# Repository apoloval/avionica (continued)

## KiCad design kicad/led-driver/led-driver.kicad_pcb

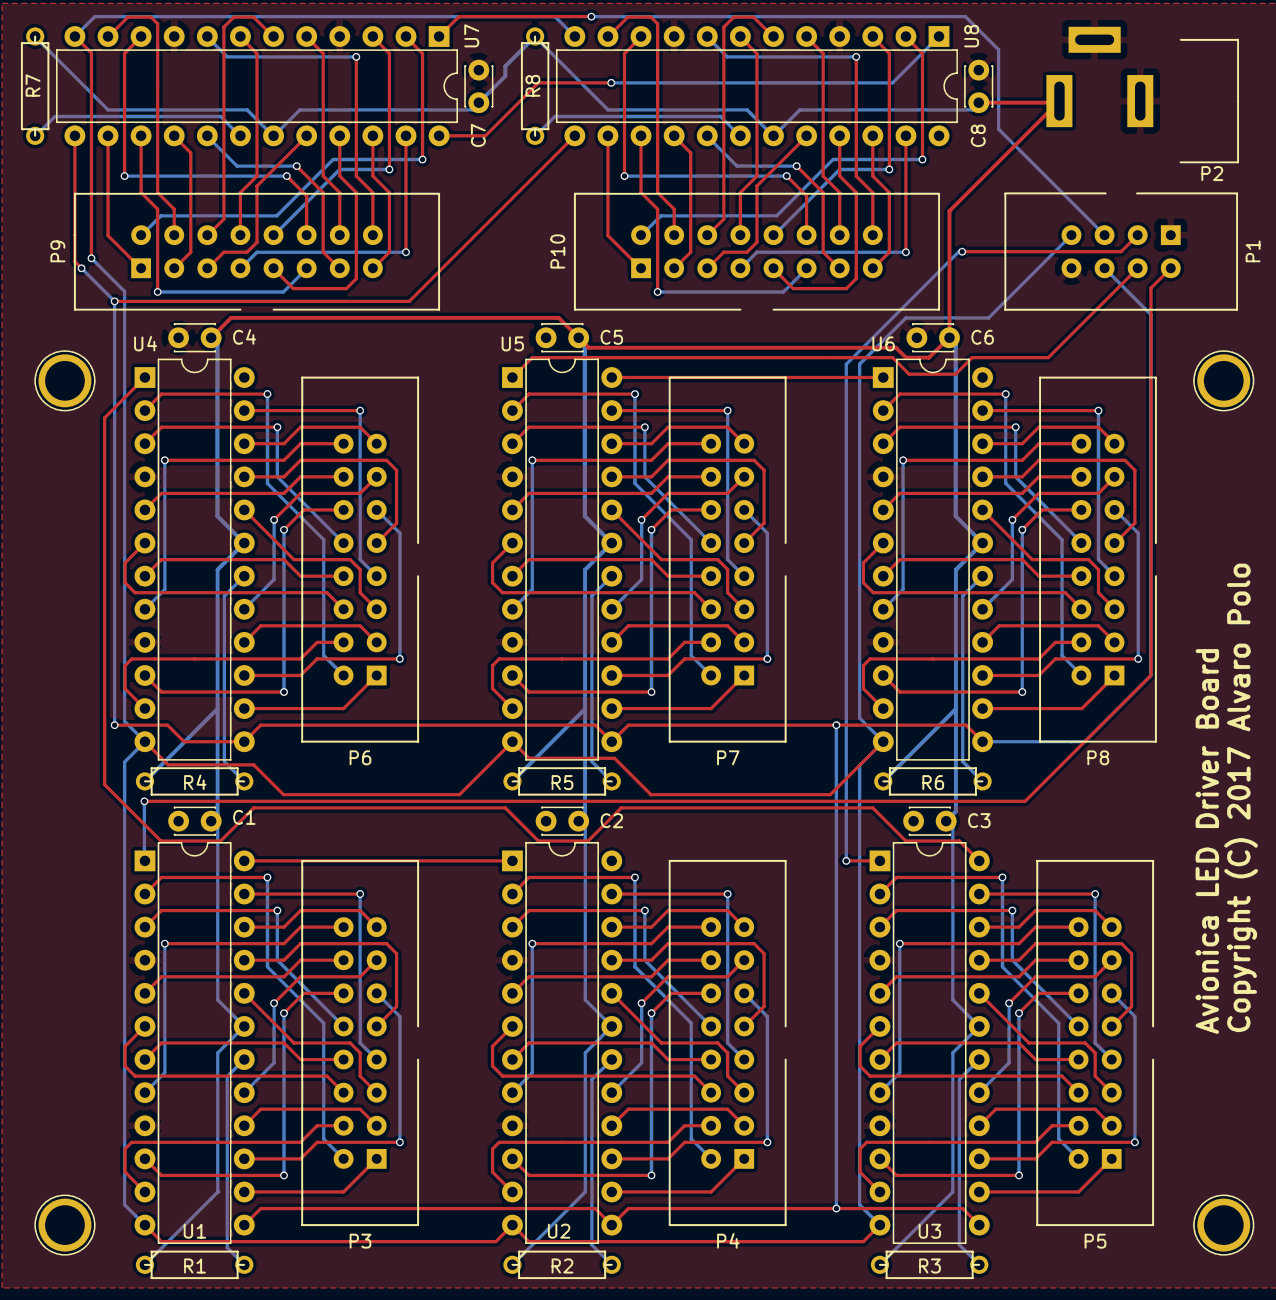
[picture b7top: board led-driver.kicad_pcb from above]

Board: 2 copper layers, 34 parts (0 on the bottom side), 148 nets.

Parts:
C1, C2, C3, C4, C5, C6, C7, C8: C_Small; C_Disc_D3.0mm_W2.0mm_P2.50mm
P1: CONN_02X04; idc-8p
P2: CONN_01X03; Jack_55_21
P3, P4, P5, P6, P7, P8, P9, P10: CONN_02X08; idc-16p
R1, R2, R3, R4, R5, R6, R7, R8: R; R3
U1, U2, U3, U4, U5, U6, U7, U8: MAX7219; DIP-24_W7.62mm

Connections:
/CLOCK: P1.6, U1.13, U2.13, U3.13, U4.13, U5.13, U6.13, U7.13, U8.13
/LATCH: P1.7, U1.12, U2.12, U3.12, U4.12, U5.12, U6.12, U7.12, U8.12
/LINE-A/DIG.1.0: P3.2, U1.2
/LINE-A/DIG.1.1: P3.4, U1.11
/LINE-A/DIG.1.2: P3.6, U1.6
/LINE-A/DIG.1.3: P3.8, U1.7
/LINE-A/DIG.1.4: P3.10, U1.3
/LINE-A/DIG.1.5: P3.12, U1.10
/LINE-A/DIG.1.6: P3.14, U1.5
/LINE-A/DIG.1.7: P3.16, U1.8
/LINE-A/DIG.2.0: P4.2, U2.2
/LINE-A/DIG.2.1: P4.4, U2.11
/LINE-A/DIG.2.2: P4.6, U2.6
/LINE-A/DIG.2.3: P4.8, U2.7
/LINE-A/DIG.2.4: P4.10, U2.3
/LINE-A/DIG.2.5: P4.12, U2.10
/LINE-A/DIG.2.6: P4.14, U2.5
/LINE-A/DIG.2.7: P4.16, U2.8
/LINE-A/SEG1.A: P3.1, U1.14
/LINE-A/SEG1.B: P3.3, U1.16
/LINE-A/SEG1.C: P3.5, U1.20
/LINE-A/SEG1.D: P3.7, U1.23
/LINE-A/SEG1.DP: P3.15, U1.22
/LINE-A/SEG1.E: P3.9, U1.21
/LINE-A/SEG1.F: P3.11, U1.15
/LINE-A/SEG1.G: P3.13, U1.17
/LINE-A/SEG2.A: P4.1, U2.14
/LINE-A/SEG2.B: P4.3, U2.16
/LINE-A/SEG2.C: P4.5, U2.20
/LINE-A/SEG2.D: P4.7, U2.23
/LINE-A/SEG2.DP: P4.15, U2.22
/LINE-A/SEG2.E: P4.9, U2.21
/LINE-A/SEG2.F: P4.11, U2.15
/LINE-A/SEG2.G: P4.13, U2.17
/LINE-B/DIG.1.0: P5.2, U3.2
/LINE-B/DIG.1.1: P5.4, U3.11
/LINE-B/DIG.1.2: P5.6, U3.6
/LINE-B/DIG.1.3: P5.8, U3.7
/LINE-B/DIG.1.4: P5.10, U3.3
/LINE-B/DIG.1.5: P5.12, U3.10
/LINE-B/DIG.1.6: P5.14, U3.5
/LINE-B/DIG.1.7: P5.16, U3.8
/LINE-B/DIG.2.0: P6.2, U4.2
/LINE-B/DIG.2.1: P6.4, U4.11
/LINE-B/DIG.2.2: P6.6, U4.6
/LINE-B/DIG.2.3: P6.8, U4.7
/LINE-B/DIG.2.4: P6.10, U4.3
/LINE-B/DIG.2.5: P6.12, U4.10
/LINE-B/DIG.2.6: P6.14, U4.5
/LINE-B/DIG.2.7: P6.16, U4.8
/LINE-B/SEG1.A: P5.1, U3.14
/LINE-B/SEG1.B: P5.3, U3.16
/LINE-B/SEG1.C: P5.5, U3.20
/LINE-B/SEG1.D: P5.7, U3.23
/LINE-B/SEG1.DP: P5.15, U3.22
/LINE-B/SEG1.E: P5.9, U3.21
/LINE-B/SEG1.F: P5.11, U3.15
/LINE-B/SEG1.G: P5.13, U3.17
/LINE-B/SEG2.A: P6.1, U4.14
/LINE-B/SEG2.B: P6.3, U4.16
/LINE-B/SEG2.C: P6.5, U4.20
/LINE-B/SEG2.D: P6.7, U4.23
/LINE-B/SEG2.DP: P6.15, U4.22
/LINE-B/SEG2.E: P6.9, U4.21
/LINE-B/SEG2.F: P6.11, U4.15
/LINE-B/SEG2.G: P6.13, U4.17
/LINE-C/DIG.1.0: P7.2, U5.2
/LINE-C/DIG.1.1: P7.4, U5.11
/LINE-C/DIG.1.2: P7.6, U5.6
/LINE-C/DIG.1.3: P7.8, U5.7
/LINE-C/DIG.1.4: P7.10, U5.3
/LINE-C/DIG.1.5: P7.12, U5.10
/LINE-C/DIG.1.6: P7.14, U5.5
/LINE-C/DIG.1.7: P7.16, U5.8
/LINE-C/DIG.2.0: P8.2, U6.2
/LINE-C/DIG.2.1: P8.4, U6.11
/LINE-C/DIG.2.2: P8.6, U6.6
/LINE-C/DIG.2.3: P8.8, U6.7
/LINE-C/DIG.2.4: P8.10, U6.3
/LINE-C/DIG.2.5: P8.12, U6.10
/LINE-C/DIG.2.6: P8.14, U6.5
/LINE-C/DIG.2.7: P8.16, U6.8
/LINE-C/SEG1.A: P7.1, U5.14
/LINE-C/SEG1.B: P7.3, U5.16
/LINE-C/SEG1.C: P7.5, U5.20
/LINE-C/SEG1.D: P7.7, U5.23
/LINE-C/SEG1.DP: P7.15, U5.22
/LINE-C/SEG1.E: P7.9, U5.21
/LINE-C/SEG1.F: P7.11, U5.15
/LINE-C/SEG1.G: P7.13, U5.17
/LINE-C/SEG2.A: P8.1, U6.14
/LINE-C/SEG2.B: P8.3, U6.16
/LINE-C/SEG2.C: P8.5, U6.20
/LINE-C/SEG2.D: P8.7, U6.23
/LINE-C/SEG2.DP: P8.15, U6.22
/LINE-C/SEG2.E: P8.9, U6.21
/LINE-C/SEG2.F: P8.11, U6.15
/LINE-C/SEG2.G: P8.13, U6.17
/LINE-D/DIG.1.0: P9.2, U7.2
/LINE-D/DIG.1.1: P9.4, U7.11
/LINE-D/DIG.1.2: P9.6, U7.6
/LINE-D/DIG.1.3: P9.8, U7.7
/LINE-D/DIG.1.4: P9.10, U7.3
/LINE-D/DIG.1.5: P9.12, U7.10
/LINE-D/DIG.1.6: P9.14, U7.5
/LINE-D/DIG.1.7: P9.16, U7.8
/LINE-D/DIG.2.0: P10.2, U8.2
/LINE-D/DIG.2.1: P10.4, U8.11
/LINE-D/DIG.2.2: P10.6, U8.6
/LINE-D/DIG.2.3: P10.8, U8.7
/LINE-D/DIG.2.4: P10.10, U8.3
/LINE-D/DIG.2.5: P10.12, U8.10
/LINE-D/DIG.2.6: P10.14, U8.5
/LINE-D/DIG.2.7: P10.16, U8.8
/LINE-D/SEG1.A: P9.1, U7.14
/LINE-D/SEG1.B: P9.3, U7.16
/LINE-D/SEG1.C: P9.5, U7.20
/LINE-D/SEG1.D: P9.7, U7.23
/LINE-D/SEG1.DP: P9.15, U7.22
/LINE-D/SEG1.E: P9.9, U7.21
/LINE-D/SEG1.F: P9.11, U7.15
/LINE-D/SEG1.G: P9.13, U7.17
/LINE-D/SEG2.A: P10.1, U8.14
/LINE-D/SEG2.B: P10.3, U8.16
/LINE-D/SEG2.C: P10.5, U8.20
/LINE-D/SEG2.D: P10.7, U8.23
/LINE-D/SEG2.DP: P10.15, U8.22
/LINE-D/SEG2.E: P10.9, U8.21
/LINE-D/SEG2.F: P10.11, U8.15
/LINE-D/SEG2.G: P10.13, U8.17
/LINE.A: P1.2, U1.1
/LINE.B: P1.3, U3.1
/LINE.C: P1.4, U5.1
/LINE.D: P1.5, U7.1
GND: C1.2, C2.2, C3.2, C4.2, C5.2, C6.2, C7.2, C8.2, P1.1, P1.8, P2.2, P2.3, U1.4, U1.9, U2.4, U2.9, U3.4, U3.9, U4.4, U4.9, U5.4, U5.9, U6.4, U6.9, U7.4, U7.9, U8.4, U8.9
unnamed: R1.2, U1.18
unnamed: R2.2, U2.18
unnamed: R3.2, U3.18
unnamed: R4.2, U4.18
unnamed: R5.2, U5.18
unnamed: R6.2, U6.18
unnamed: R7.2, U7.18
unnamed: R8.2, U8.18
unnamed: U1.24, U2.1
unnamed: U3.24, U4.1
unnamed: U5.24, U6.1
unnamed: U7.24, U8.1
VCC: C1.1, C2.1, C3.1, C4.1, C5.1, C6.1, C7.1, C8.1, P2.1, R1.1, R2.1, R3.1, R4.1, R5.1, R6.1, R7.1, R8.1, U1.19, U2.19, U3.19, U4.19, U5.19, U6.19, U7.19, U8.19

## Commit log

2016-02-10 Make it so
2016-02-10 Introduce Avionica library for Arduino
    With just minor functionality implemented.
2016-02-10 Improve `Avionica::Device` type in Arduino library
    The plan is to let the user to define different devices and declare
    the interactions of each device in a separate file.
2016-02-10 Reduce max number of devices for Arduino Uno
    To save RAM, limit them to 12. Actually the physical limit.
2016-02-11 Simplify private methods in Arduino library
2016-02-11 Introduce Avionica serial console in Arduino library
2016-02-11 Implement event interception in serial console mode for Arduino
2016-02-11 Rename console mode to debug mode in Arduino library
2016-02-14 New directory layout for Arduino libraries
    Putting all libraries in `arduino/libraries` will allocate space for
    more libraries.
2016-02-14 Fix typos in `BeforeInstall.txt`
2016-02-14 Move debug mode enabling to `begin()` function in Arduino library
2016-02-14 Integrate Avionica with Arduino OACSP library
2016-02-14 Add the ability to notify LVAR & FSUIPC events on devices
2016-02-15 Initialize OACSP from Avionica `begin()`
2016-02-15 Send reset command on device begin for Arduino library
2016-02-15 Update copyright notes in source files
2016-02-15 Introduce Avionica SPI for PIC microcontrollers
    A header file that can be included from XC8 projects to manage SPI.
2016-02-17 Add a README file for Arduino library
2016-02-18 Introduce basic structure of engine start panel device
2017-01-24 Make it so
    Import the existing files prior to have a Git repository.
2017-01-24 Add a mostly placeholder README file
2017-06-24 Add a gitignore file
2017-06-24 Adapt avionica ports to 6 pins
2017-06-24 Move Kicad files into its own subdir
2017-06-24 Add some VHDL files to simulate the modules
    By now, just an entity to simulate 74595 ICs. More coming in the future.
2017-06-24 VHDL: replace process by binding for 74595
2017-06-24 Make VHDL Makefile more robust
    Make it build when any dependency changes.
2017-06-24 VHDL: Add the serial out pin of 74595
2017-06-24 VHDL: clarify pin names in 74595
    Use the names from NXP datasheet and simplify the testbench.
2017-06-24 VHDL: add a new entity for 4021 parallel in serial out shift register
2017-06-26 Introduce scaffolding of a new PCB: A320 ECAM panel
2017-06-26 Initial schematic for A320 ECAM panel
2017-06-27 Adda RC circuit for CLR push buttons to debounce
2017-06-30 Use a polarized capacitor for CLR button of ECAM panel
2017-07-02 Use polarized cap for MM74C922's debounce in ECAM panel
2017-07-12 Fix Inverted columns and rows in 74C922 for ECAM panel
2017-07-12 Fix segment connections from MAX7219 in ECAM panel
2017-07-12 Add potentiometers to control ECAM display bright
    And also, reorganize the schematic to separate the different subsets of components.
2017-07-13 Add backlighting LEDs and power connectors to ECAM panel
2017-07-14 Fix wrong path to the Avionica module in A320 ECAM panel
2017-07-14 Add an axial resistor to the Avionica module
2017-07-14 Add a LED SMD 1210 to the Avionica module
2017-07-14 Add a disc capacitor to the Avionica module
2017-07-14 Add a radial capacitor to the Avionica module
2017-07-14 Add a Omron B3F push button to the Avionica module
2017-07-14 Add some pin headers to the Avionica module
2017-07-14 Add some associations to footprints in A320 ECAM panel
2017-07-14 Add some DIP housings to the Avionica module
2017-07-14 Replace power connectors by 3-line ones
    One for anode, two for cathode.
2017-07-14 Add the remaining footprint associations in A320 ECAM panel
2017-07-14 Add M3 mounting hole to the Avionica module
2017-07-28 Move potentiometer schematic to Avionica module
2017-07-28 Add a new Kicad project for a A320 engine start panel
2017-07-28 Add a rotary switch of 3 positions to the Avionica library
2017-07-28 Make the VCC pin non-visible in MAX7219
2017-07-28 Remove backup and cache files
2017-07-28 Prevent cached and backup files to be checkout
2017-07-28 Preliminary work on A320 ECAM panel PCB
2017-07-28 Adjust footprints layout in A320 ECAM panel
2017-07-28 Include some other backup files in the gitignore
2017-08-01 Make some final adjustments on footprints for A320 ECAM panel
2017-08-01 Complete the tracks of the PCB in A320 ECAM panel
2017-08-02 Include all necessary layers in plot selection for A320 ECAM panel
2017-09-30 Fix missing tracks in A320 ECAM panel
2017-09-30 Fix wrong width of Omron B3F pads
2017-09-30 Fix more missing pads in A320 ECAM panel
2017-09-30 Minor issues and label fixings in A320 ECAM panel
2017-10-08 Several changes in avionica library
    * Add 74125 part (3-state buffer)
    * Change the position of data pins in 74922
    * Set VCC pin as non-visible for MAX7219
2017-10-08 Add schematic for a IO Controller board
2017-10-08 Add a DIP-14 header for Avionica module
2017-10-08 Assign footprints for IO Controller board
2017-10-09 Ignore net files
2017-10-11 Simplify the IO Controller board schematics
2017-10-12 Fix several footprints to hide or remove undesired labels
2017-10-12 Several fixes in IO Controller board schematics
    * Remove extra unneeded decoupling capacitors.
    * Fix wrong orientation of dielectric capacitors
2017-10-12 First version of IO Controller panel PCB
2017-10-12 Add mounting holes to the IO Controller PCB
2017-10-12 Fix relative links to 3D models for several modules
2017-10-12 Add several layers in silkscreen for IO Controller board PCB
2017-10-12 Hide component label in IDC 10P footprint
2017-10-12 Use a single IDC10 connector for switches in IO Controller board
2017-10-12 Complete connections of IO Controller board PCB
2017-10-13 Add a new module for a IDC 6P angled
2017-10-13 Add OSHW logo to IO Controller board and fix some labels
2017-10-13 Use more appropriate models for capacitor footprints
2017-10-14 Fix non-DAVed key controllers problem in IO Controller board
2017-10-25 Add atmega328 microcontroller to the library
2017-10-25 Add a crystal component to Avionica library
2017-10-25 Fix wrong pin in atmega328
2017-10-25 Add a capacitor component to the Avionica library
2017-10-25 Add a connector of 6pins to Avionica library
2017-10-25 Add a connector of 3 pins to Avionica library
2017-10-25 A a crystal footprint for Avionica module
2017-10-25 Add a DIP-28 footprint for Avionica module
2017-10-25 Change the schematics of keypad controller to use an ATmega328
2017-10-25 Remove Avionica library DCM file
    It's only used for descriptions we don't really need.
2017-10-25 Add a resistor to the Avionica library
2017-10-25 Add a 8pin connector to the Avionica library
2017-10-25 Add 3D model for DIP-28 housing
2017-10-25 Add a MAX7219 to the keypad controller
2017-10-25 Prepare the layout of the Keypad Controller PCB
2017-11-01 Add the tracks to the Keypad Controller PCB
2017-11-01 Introduce a DAV signal in the Keypad Controller board
2017-11-01 Better alignment of oscillator capacitors in Keypad PCB
2017-11-01 Add a new component and module for a IDC 12P connector
2017-11-01 Replace 2x6p IDC connectors by a single 12p in Keypad Controller board
2017-11-01 Add a 12p connector to the Avionica library
2017-11-01 Replace 2x8p IDC connectors by a single 16p in Keypad Controller board
2017-11-01 Fix several issues in some footprints
2017-11-01 Add a LED component to the Avionica library
2017-11-01 Add a status LED to the Keypad Controller board
2017-11-01 Rename the files of Keypad Controller board
2017-11-23 Set some PCB printing settings for Keypad Controller board
2017-11-24 Introduce a Arduino sketch for the Avionica firmware
2017-12-29 Make Avionica firmware to send a connection header after setup
    It will be useful for the PC to wait for the board to be up and running and detect it is an actual Avionica board.
2017-12-29 Increase the drill size of IDC connectors
2017-12-29 Keypad controller Rev02: Update IDC connectors
2017-12-29 Use a directory layout to accomodate for new firmwares
    The main firmware we had corresponds to what we will call the Motherboard.
2017-12-29 Use explicit SPI settings in Motherboard firmware
    So we are sure about the modes we are using.
2017-12-29 Fix wrong read of input message in Motherboard firmware
2017-12-30 Fix wrong connection of ISET pin in Keypad Controller
2017-12-30 Add conn02 and conn04 to the Avionica lib
2017-12-30 Fix wrong link to 3d model for kf2510 connectors
2017-12-30 Update modules credits
2017-12-31 Introduce the new brand IO Board
    As a derived work from Keypad Controller, just changing the firmware you can convert this IO Board into a keypad controller, a ADC, a rotary switch controller, a general input controller... etc. One 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
2017-12-31 Add initial version of the Motherboard
2017-12-31 Fix port references in Motherboard
    So they match the port names
2017-12-31 Fix some aesthetical paths in Motherboard
2017-12-31 Update plot settings for Motherboard
2017-12-31 Remove legacy and unused projects
